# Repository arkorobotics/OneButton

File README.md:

# OneButton

The OneButton is a programmable single-key USB Keyboard with RGB LED's.

The OneButton serves no single purpose, but rather is designed to be programmed for multiple uses.

Possible Applications: 
- Generate pre-scripted USB keystrokes (included in the example code)
- Serve as a "Soft" E-STOP button with color LED's to indicate state
- Interface with a desktop API to perform other actions (i.e. - Indiciate a new Tweet notification by turning LED's Blue. Pressing the key opens Twitter.)
- The possiblities are not endless!

The OneButton includes six programmable RGB LED's because everyone loves blinky lights! <br>

...and easter eggs!<br>

Included in this GitHub:
- Firmware: Example code written in C++ and Rust 
- Hardware: Schematic, Board, Gerber, and 3D printable enclosure CAD files

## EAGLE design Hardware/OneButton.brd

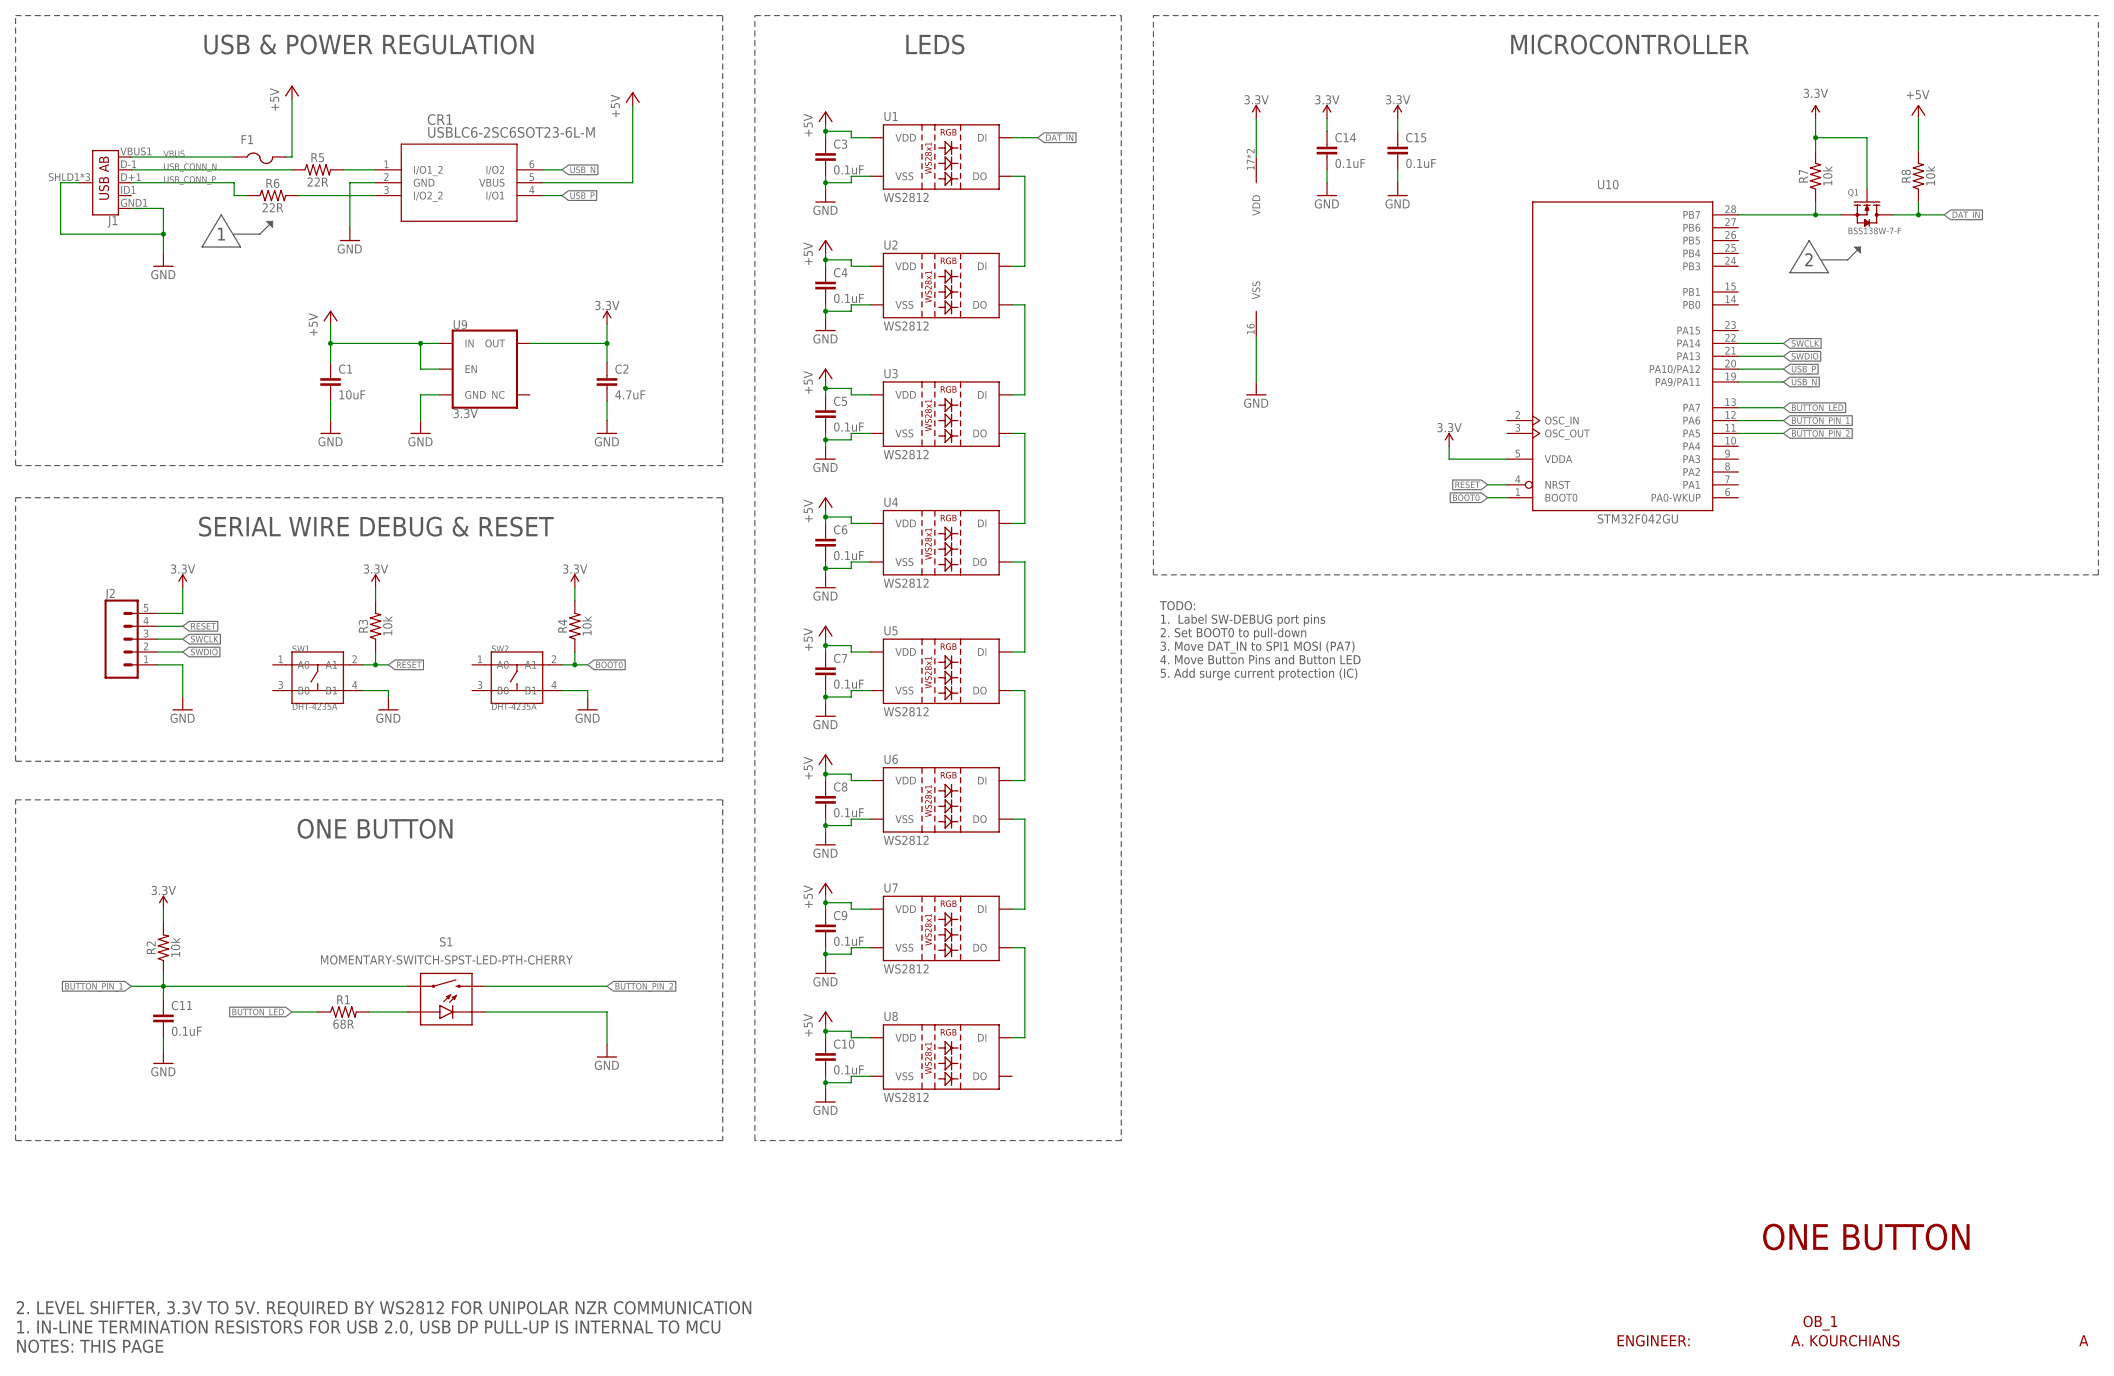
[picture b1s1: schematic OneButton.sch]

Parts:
C1: 10uF; CAP-1206
C2: 4.7uF; CAP-1206
C3, C4, C5, C6, C7, C8, C9, C10, C11, C14, C15: 0.1uF; CAP-0603
CR1: USBLC6-2SC6SOT23-6L-M; SOT23-6L-M
F1: PTCFUSE-1206; R1206
J1: USB_AB_SMT; USB-AB-MICRO-SMD
J2: CONN_05; 1X05
Q1: BSS138W-7-F; SOT-23
R1: 68R; RESC0603_N
R2, R3, R4, R7, R8: 10k; RESC0603_N
R5, R6: 22R; RESC0603_N
S1: MOMENTARY-SWITCH-SPST-LED-PTH-CHERRY; CHERRY-MX-LED
SW1, SW2: DHT-4235A; SW4-SMD-4.2X3.2X2.5MM
U1, U2, U3, U4, U5, U6, U7, U8: WS2812; LED-TRICOLOR-5050-IC
U9: 3.3V; SOT23-5
U10: STM32F042GU; UFQFPN28

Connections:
3.3V: C2.1, C14.1, C15.1, J2.5, Q1.1 (G), R2.2, R3.2, R4.2, R7.2, U9.5 (OUT), U10.5 (VDDA), U10.17 (VDD), U10.18 (VDD)
+5V: C1.1, C3.1, C4.1, C5.1, C6.1, C7.1, C8.1, C9.1, C10.1, CR1.5 (VBUS), F1.2, R8.2, U1.3 (VDD), U1.5 (VDD), U2.3 (VDD), U2.5 (VDD), U3.3 (VDD), U3.5 (VDD), U4.3 (VDD), U4.5 (VDD), U5.3 (VDD), U5.5 (VDD), U6.3 (VDD), U6.5 (VDD), U7.3 (VDD), U7.5 (VDD), U8.3 (VDD), U8.5 (VDD), U9.1 (IN), U9.3 (EN)
BOOT0: R4.1, SW2.2 (A1), U10.1 (BOOT0)
BUTTON_LED: R1.1, U10.13 (PA7)
BUTTON_PIN_1: C11.1, R2.1, S1.S1 (1), U10.12 (PA6)
BUTTON_PIN_2: S1.S2 (2), U10.11 (PA5)
DAT_IN: Q1.3 (D), R8.1, U1.2 (DI)
GND: C1.2, C2.2, C3.2, C4.2, C5.2, C6.2, C7.2, C8.2, C9.2, C10.2, C11.2, C14.2, C15.2, CR1.2 (GND), J1.GND1 (GND), J1.SHLD1 (SHIELD), J1.SHLD2 (SHIELD), J1.SHLD3 (SHIELD), J2.1, S1.K (C), S1.K1 (C), SW1.4 (B1), SW2.4 (B1), U1.6 (VSS), U2.6 (VSS), U3.6 (VSS), U4.6 (VSS), U5.6 (VSS), U6.6 (VSS), U7.6 (VSS), U8.6 (VSS), U9.2 (GND), U10.16 (VSS)
unnamed: Q1.2 (S), R7.1, U10.28 (PB7)
unnamed: R1.2, S1.A, S1.A1 (A)
unnamed: U1.1 (DO), U2.2 (DI)
unnamed: U2.1 (DO), U3.2 (DI)
unnamed: U3.1 (DO), U4.2 (DI)
unnamed: U4.1 (DO), U5.2 (DI)
unnamed: U5.1 (DO), U6.2 (DI)
unnamed: U6.1 (DO), U7.2 (DI)
unnamed: U7.1 (DO), U8.2 (DI)
RESET: J2.4, R3.1, SW1.2 (A1), U10.4 (NRST)
SWCLK: J2.3, U10.22 (PA14)
SWDIO: J2.2, U10.21 (PA13)
USB_CONN_N: J1.D-1 (D-), R5.1
USB_CONN_P: J1.D+1 (D+), R6.1
USB_N: CR1.6 (I/O2), U10.19 (PA9/PA11)
USB_P: CR1.4 (I/O1), U10.20 (PA10/PA12)
USB_R_N: CR1.1 (I/O1_2), R5.2
USB_R_P: CR1.3 (I/O2_2), R6.2
VBUS: F1.1, J1.VBUS1 (VBUS)

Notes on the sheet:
ONE BUTTON
ENGINEER: A. KOURCHIANS
OB_1
USB & POWER REGULATION
SERIAL WIRE DEBUG & RESET
LEDS
MICROCONTROLLER
2. LEVEL SHIFTER, 3.3V TO 5V. REQUIRED BY WS2812 FOR UNIPOLAR NZR COMMUNICATION 1. IN-LINE TERMINATION RESISTORS FOR USB 2.0, USB DP PULL-UP IS INTERNAL TO MCU NOTES: THIS PAGE
TODO: 1. Label SW-DEBUG port pins 2. Set BOOT0 to pull-down 3. Move DAT_IN to SPI1 MOSI (PA7) 4. Move Button Pins and Button LED 5. Add surge current protection (IC)

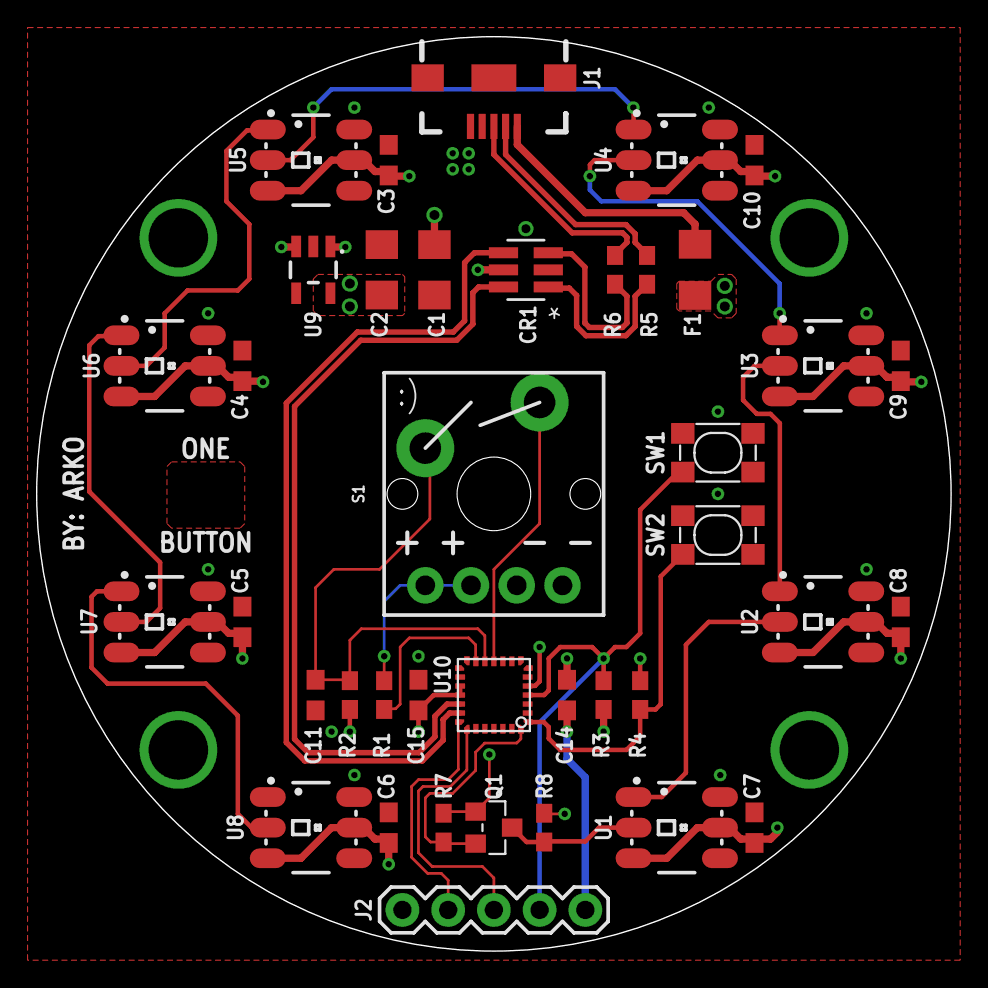
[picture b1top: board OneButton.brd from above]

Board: 4 copper layers, 50.8 x 50.8 mm, 39 parts (0 on the bottom side), 27 nets.

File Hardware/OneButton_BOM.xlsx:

Qty | Value | Device | Package | Parts | Description | MPN | Cost | Link
1 |  | CONN_05 | 1X05 | J2 | Multi connection point. Often used as Generic Header-pin footprint for 0.1 inch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 | 61300511121 | 0.25 | https://www.digikey.com/product-detail/en/wurth-electronics-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
1 |  | PTCFUSE-1206 | R1206 | F1 | PTC fuses, resettable thermistors | 0ZCG0075FF2C | 0.13 | https://www.digikey.com/product-detail/en/bel-fuse-inc/0ZCG0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
1 |  | USB_AB_SMT | USB-AB-MICRO-SMD | J1 | USB Type AB Micro Connector | 10118192-0001LF | 0.46 | https://www.digikey.com/product-detail/en/amphenol-fci/10118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
10 | 0.1uF | 0.1UFCAP-0603 | CAP-0603 | C3, C4, C5, C6, C7, C8, C9, C10, C14, C15 | 0.1µF ceramic capacitors | C0603C104K8RACTU | 2.9000000000000001E-2 | https://www.digikey.com/product-detail/en/kemet/C0603C104K8R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
4 | 10k | RESISTORRES-0603 | RESC0603_N | R3, R4, R7, R8 | Generic Resistor Package | RC0603JR-0710KL | 4.3999999999999997E-2 | https://www.digikey.com/product-detail/en/yageo/RC0603JR-071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
1 | 10uF | 10UFCAP-1206 | CAP-1206 | C1 | 10.0µF ceramic capacitors | CL31B106KAHNNNE | 0.26 | https://www.digikey.com/product-detail/en/samsung-electro-me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
2 | 22R | RESISTORRES-0603 | RESC0603_N | R5, R6 | Generic Resistor Package | RC0603JR-0722RL | 2.1999999999999999E-2 | https://www.digikey.com/product-detail/en/yageo/RC0603JR-072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
1 | 3.3V | V_REG_AP2112K-3.3V | SOT23-5 | U9 | AP2112 - 600mA CMOS LDO Regulator w/ Enable | AP2112K-3.3TRG1 | 0.48 | https://www.digikey.com/product-detail/en/diodes-incorporate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
1 | 4.7uF | 4.7UFCAP-1206 | CAP-1206 | C2 | 4.7µF ceramic capacitors | C3216X7R1C475K160AB | 0.27 | https://www.digikey.com/product-detail/en/tdk-corporation/C3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
1 | 68R | RESISTORRES-0603 | RESC0603_N | R1 | Generic Resistor Package | RC0603JR-0768RL | 0.1 | https://www.digikey.com/product-detail/en/yageo/RC0603JR-076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
1 | BSS138W-7-F | SMD-MOSFET-N-CH-50V-200MA-BSS138W-7-F(SOT-23) | SOT-23 | Q1 | SMD-MOSFET-N-CH | BSS138LT1G | 0.28999999999999998 | https://www.digikey.com/product-detail/en/on-semiconductor/B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
2 | DHT-4235A | SMD-BUTTON-TOP-DHT-4235A(4P-4.2X3.2MM) | SW4-SMD-4.2X3.2X2.5MM | SW1, SW2 | 311020045 | PTS810 SJK 250 SMTR LFS | 0.56000000000000005 | https://www.digikey.com/product-detail/en/c-k/PTS810-SJK-250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
1 | DNP | CAPACITORCAP-0603 | CAP-0603 | C11 | Generic chip capacitor | - | - | -
1 | DNP | RESISTORRES-0603 | RESC0603_N | R2 | Generic Resistor Package | - | - | -
1 | MOMENTARY-SWITCH-SPST-LED-PTH-CHERRY | MOMENTARY-SWITCH-SPST-LED-PTH-CHERRY | CHERRY-MX-LED | S1 | Momentary Switch (Pushbutton) - SPST - w/ LED | MX1A-E1NW | 0.9 | https://www.digikey.com/product-detail/en/cherry-americas-ll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
1 | STM32F042GU | STM32F042GU | UFQFPN28 | U10 |  | STM32F042G6U6 | 2.4500000000000002 | https://www.digikey.com/product-detail/en/stmicroelectronics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
1 | USBLC6-2SC6SOT23-6L-M | USBLC6-2SC6SOT23-6L-M | SOT23-6L-M | CR1 |  | USBLC62SC6 | 0.42 | https://www.digikey.com/product-detail/en/stmicroelectronics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
8 | WS2812 | WS2812";LED-TRICOLOR-5050-IC" |  | U1, U2, U3, U4, U5, U6, U7, U8 | WS2812 RGB LED w/ WS2811 driver | WS2812 | 0.5 | https://www.sparkfun.com/products/11821
 |  |  |  |  |  |  | 7.165

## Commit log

2017-11-20 Initial Commit
    Initial Commit
    Includes: Schematic, Board (unrouted), and parts lib
2017-11-26 Updated folder structure
    Updated folder structure, adding software next
2017-11-26 Updated folder structure
    Updated folder structure
2017-12-01 Rust codebase initial commit
2017-12-01 Reconfigured the folder structure
    Reconfigured the folder structure
2017-12-01 Added USB HID Library
2017-12-01 Added gitignore
    Added gitignore. Pesky build folders
2017-12-01 Removed targer folder
    Removed targer folder
2017-12-01 Updated gitignore
    Updated gitignore
2017-12-01 USB HID example builds!
    USB HID example builds!
2017-12-01 Updated readme
    Updated readme
2017-12-03 C Firmware - Hello World
    C Firmware - Hello World. TODO: Rewrite spi/uart libs, add USB lib
2017-12-03 Basic USB
    Basic USB
2017-12-04 Not sure why this is being commited
    Not sure why this is being commited
2017-12-04 I dont know
    I dont know
2017-12-19 CPP repo with working USB HID
    CPP repo with working USB HID, thanks Andy!
2017-12-21 Working USB custom HID device
    Working USB custom HID device
2017-12-23 Commit before big changes
    Commit before big changes
2017-12-27 Copied UsbCustomHid to create UsbKeyboard
    UsbKeyboard.h is currently acting a custom hid device. In the following
    commits this file will be modified to act as a usb hid keyboard.
2017-12-31 Continuously outputs "A"... YYAAAAYY!!!!!
    Working USB HID Descriptor and key press report!!!!!!!!! WOOO!!!!!
2018-01-01 Working single button press
    Remember to wait for the usb report to finish before sending the next
    one!
2018-01-08 Working SPI DMA!
    Working SPI DMA. Next we need to implement an encoder for the WS8212
    (RGB -> SPI byte buffer).
2018-01-11 Working WS8212
    Wrote some janky code that drives 8 WS8212 LED’s. Next step is to clean
    it up and move it to a library.
2018-01-13 Fixed brightness bug
    Fixed brightness bug, bad for loop counter.
2018-01-14 Code commit before creating ws8212 libs and adding cad files
    Code commit before creating ws8212 libs and adding cad files
2018-01-19 Added debug instructions, removed build files
    Added debug instructions, removed build files
2018-01-19 Cleaned up the readme
    Cleaned up the readme
2018-01-19 Removed Eagle CAD temp files
    Removed Eagle CAD temp files
2018-02-07 3D printed case update
    Updated 3D model. Button prints ESTOP when pressed.
2018-02-09 Now launches firefox!
    Fun scripting starts here…
2018-02-11 Fun demo for spec.la
    Fun demo for spec.la. Next: clean up and reorganize code into libraries
    for easy scripting.
2018-02-11 star wars edition
    star wars edition
2018-02-17 SpecLA Star Wars Demo
    SpecLA Star Wars Demo
2018-02-17 Dashboard and random colors
    Button now brings up dashboard and changes to a single random color.
2018-10-19 Mouse Wiggler
    Mouse wiggler for TVAC
2018-12-16 Spotlight branch initial commit
2018-12-23 Added delay when connecting the device
    Added delay when connecting the device
2018-12-24 Updated circuit diagram TODOs and Firmware
    Discovered that the board needs: 500mA current limiter circuit at the USB power input, 470R inline with DAT-IN, 1k between +5V and VCC, and about 200-1000uF more capacitance on +5V bus.
2018-12-28 Updated for reliability

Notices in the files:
parts and their libraries:
SparkFun-PowerSymbols: Licensing: Creative Commons ShareAlike 4.0 International - https://creativecommons.org/licenses/by-sa/4.0
